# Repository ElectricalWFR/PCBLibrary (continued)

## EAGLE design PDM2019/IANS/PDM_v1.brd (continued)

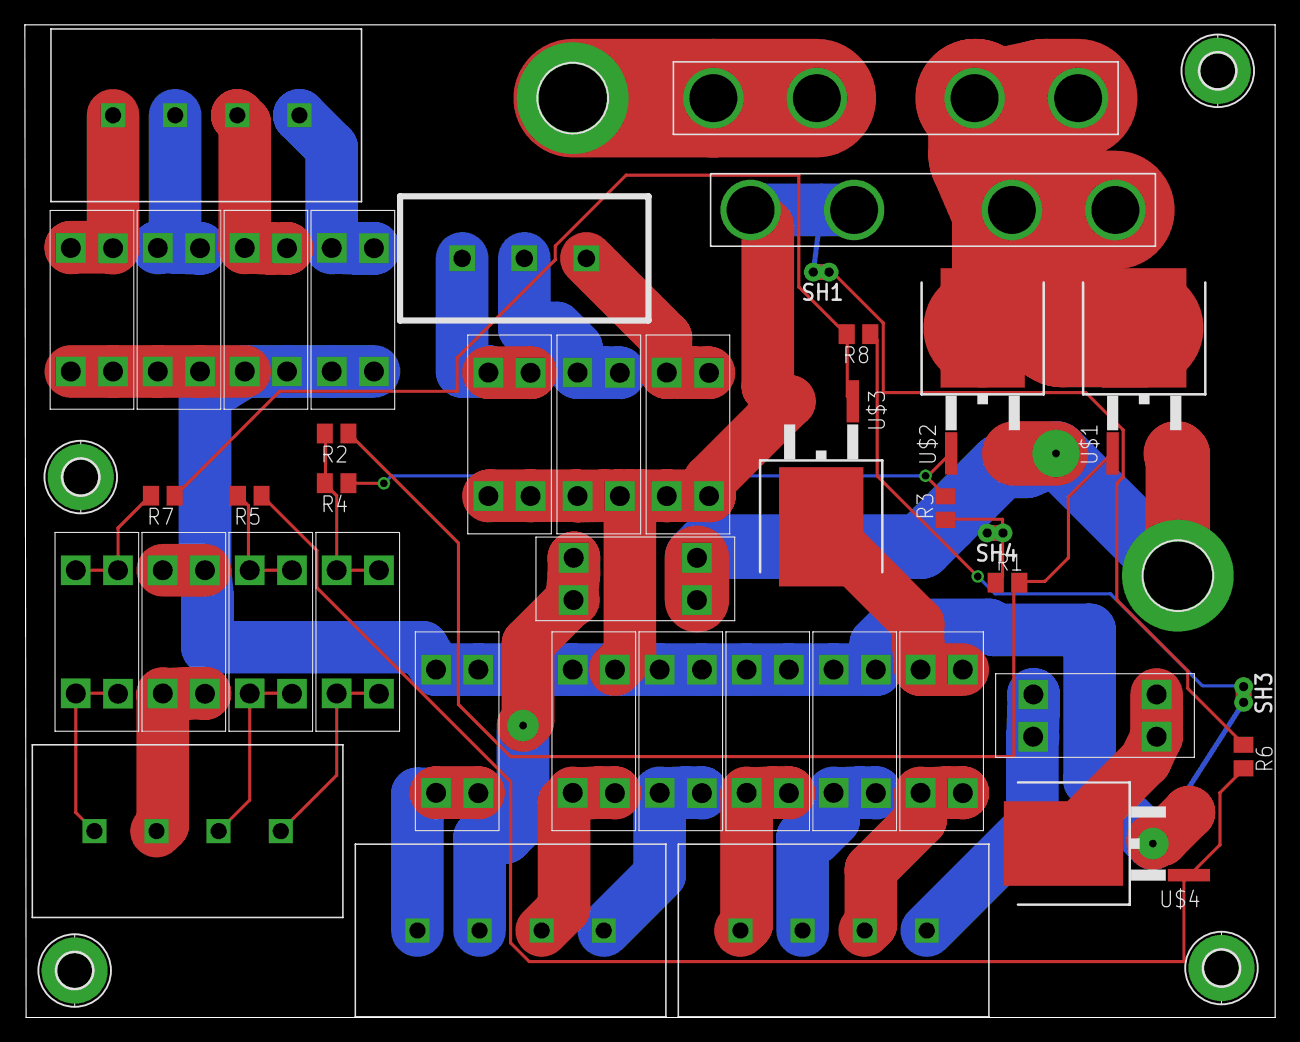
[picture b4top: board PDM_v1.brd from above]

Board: 2 copper layers, 100.6 x 79.9 mm, 47 parts (0 on the bottom side), 35 nets.

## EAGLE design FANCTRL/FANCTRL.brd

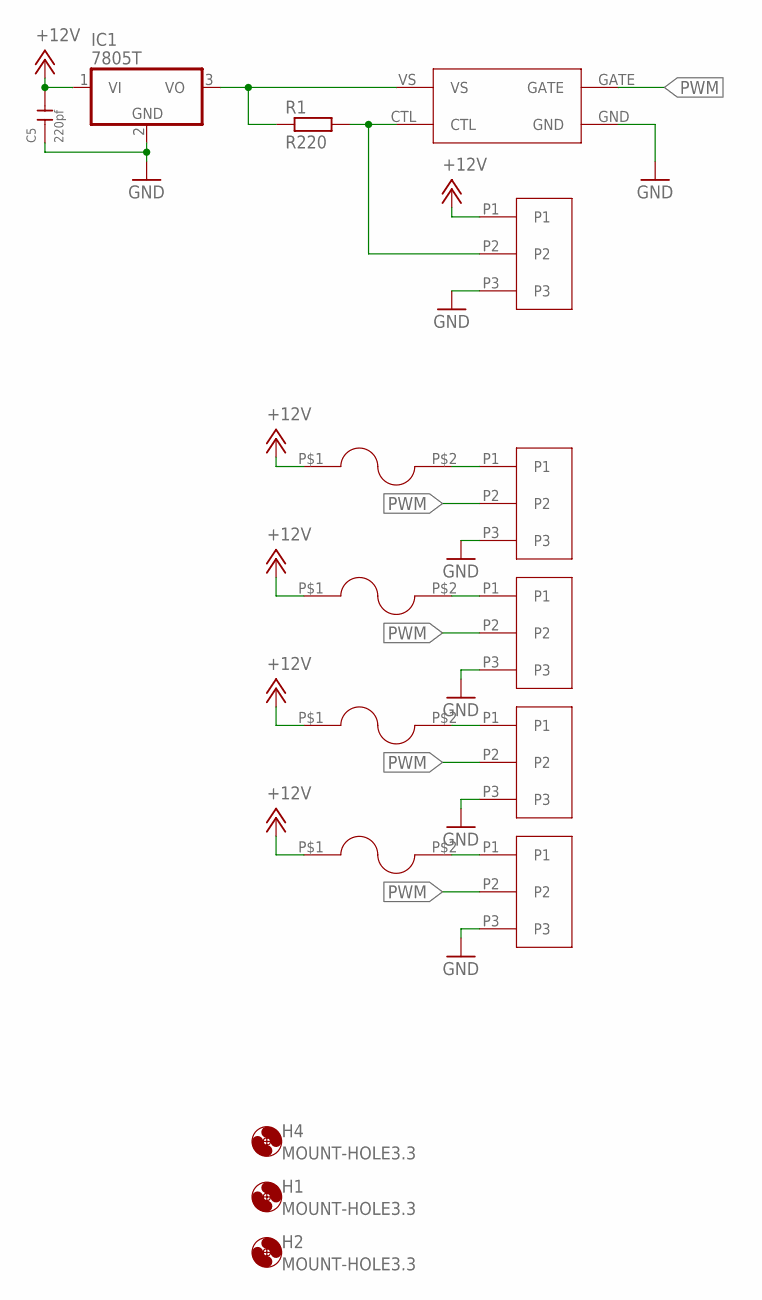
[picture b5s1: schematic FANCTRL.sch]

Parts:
C5: 220pf; C0402
H1, H2, H4: MOUNT-HOLE3.3; 3,3
IC1: 7805T; TO220H
R1: R220; R0805
U$1, U$2, U$3, U$4, U$9: 1935789
U$5, U$6, U$7, U$8: 2920L400/15MR
U$15: MIC4417; PDM_2019_REVB_MIC4416YM4-TR

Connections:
+12V: C5.2, IC1.1 (VI), U$1.P1, U$5.P$1, U$6.P$1, U$7.P$1, U$8.P$1
GND: C5.1, IC1.2 (GND), U$1.P3, U$2.P3, U$3.P3, U$4.P3, U$9.P3, U$15.GND
unnamed: U$2.P1, U$5.P$2
unnamed: U$3.P1, U$6.P$2
unnamed: U$4.P1, U$7.P$2
unnamed: U$8.P$2, U$9.P1
unnamed: IC1.3 (VO), R1.1, U$15.VS
unnamed: R1.2, U$1.P2, U$15.CTL
PWM: U$2.P2, U$3.P2, U$4.P2, U$9.P2, U$15.GATE

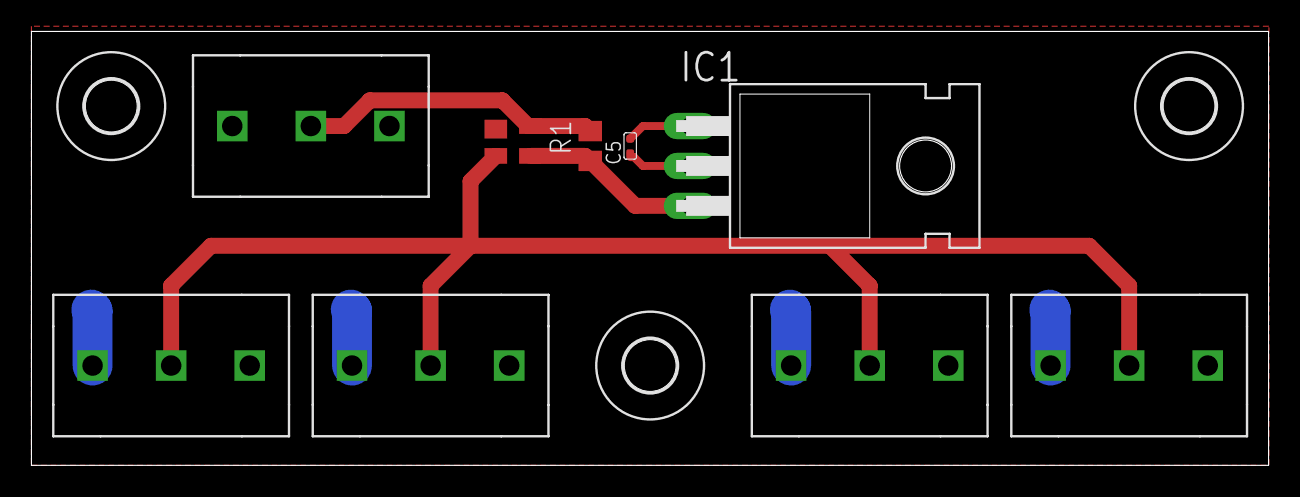
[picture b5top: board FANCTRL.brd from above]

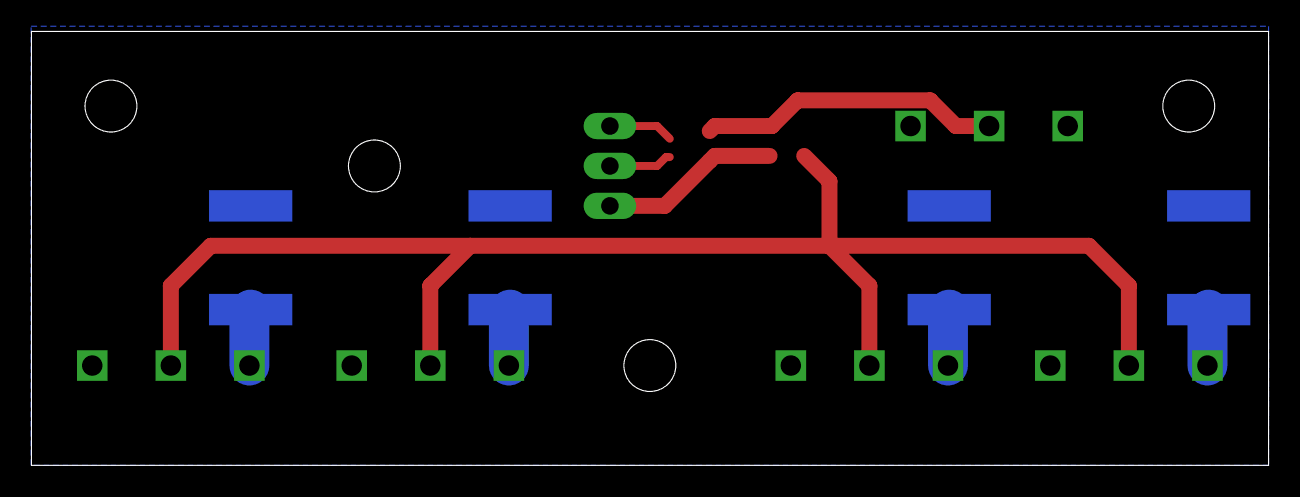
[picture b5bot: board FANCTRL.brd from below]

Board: 2 copper layers, 78.7 x 27.6 mm, 16 parts (4 on the bottom side), 9 nets.

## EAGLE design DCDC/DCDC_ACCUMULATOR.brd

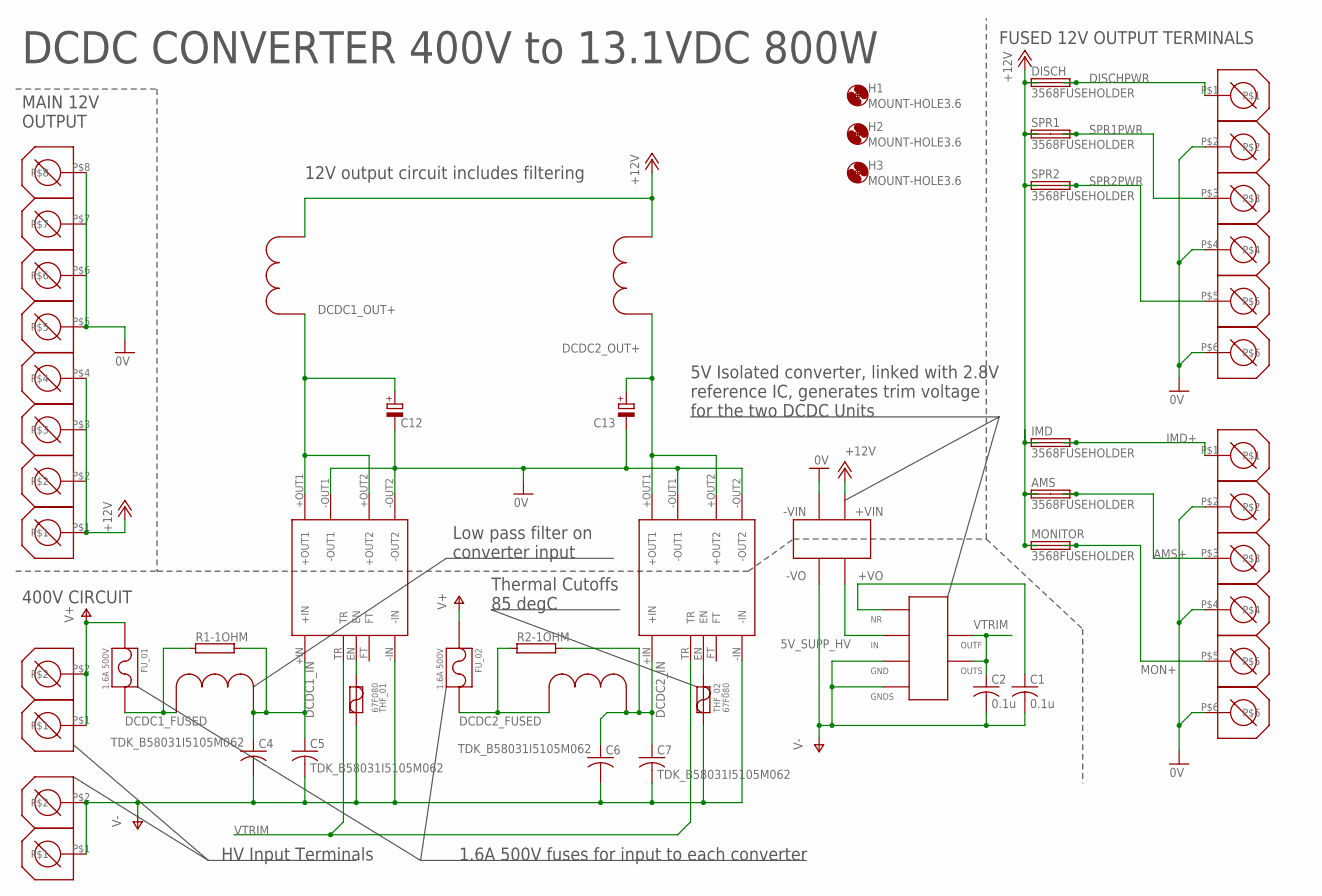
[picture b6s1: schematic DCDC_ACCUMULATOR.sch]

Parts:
AMS: 3568FUSEHOLDER; 3568
C1, C2: 0.1u; C0805
C4, C5, C6, C7: TDK_B58031I5105M062; TDK_CERALINK_USTYLE
C12, C13: CPOL-EUE7.5-16; E7,5-16
DISCH: 3568FUSEHOLDER; 3568
FU_01, FU_02: 1.6A 500V; LF_885
H1, H2, H3: MOUNT-HOLE3.6; 3,6
IMD: 3568FUSEHOLDER; 3568
MONITOR: 3568FUSEHOLDER; 3568
R1-1OHM, R2-1OHM: RMG100-V; TO-247-2V
SPR1, SPR2: 3568FUSEHOLDER; 3568
THF_01, THF_02: 67F080; TO220ACS
U$1, U$4: DCM4623TD2J13D0T00; VICOR_DCM4623TD2J13D0T00
U$2, U$5: P1330-102H; P1330
U$3, U$6: MPC1250LR36C; MPC1250LR
U$9: MURATA_MEV1S1205SC; MEV_7_PIN_SIP
U$10: MAXIM_MAX6126A28; UMAX
U$13: 1777600_PHOENIX; 1777600_FOOT
U$14, U$15: 1935200_PHOENIX; 1777587_FOOT
U$16, U$17: 282838-2_TE; 282838-2_FOOT

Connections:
0V: C12.-, C13.-, U$1.-OUT1, U$1.-OUT2, U$4.-OUT1, U$4.-OUT2, U$9.-VIN, U$13.P$5, U$13.P$6, U$13.P$7, U$13.P$8, U$14.P$2, U$14.P$4, U$14.P$6, U$15.P$2, U$15.P$4, U$15.P$6
5V_SUPP_HV: U$9.+VOUT (+VO), U$10.2 (IN)
+12V: AMS.L1 (1A), AMS.L2 (1B), DISCH.L1 (1A), DISCH.L2 (1B), IMD.L1 (1A), IMD.L2 (1B), MONITOR.L1 (1A), MONITOR.L2 (1B), SPR1.L1 (1A), SPR1.L2 (1B), SPR2.L1 (1A), SPR2.L2 (1B), U$3.P$2, U$6.P$2, U$9.+VIN, U$13.P$1, U$13.P$2, U$13.P$3, U$13.P$4
AMS+: AMS.R1 (2A), AMS.R2 (2B), U$15.P$3
DCDC1_FUSED: FU_01.P$2, R1-1OHM.1, U$2.P$1
DCDC1_IN: C4.P$1 (1), C5.P$1 (1), R1-1OHM.2, U$1.+IN, U$2.P$2
DCDC1_OUT+: C12.+, U$1.+OUT1, U$1.+OUT2, U$3.P$1
DCDC1_TEMP_DISABLE: THF_01.C, U$1.EN
DCDC2_FUSED: FU_02.P$2, R2-1OHM.1, U$5.P$1
DCDC2_IN: C6.P$1 (1), C7.P$1 (1), R2-1OHM.2, U$4.+IN, U$5.P$2
DCDC2_OUT+: C13.+, U$4.+OUT1, U$4.+OUT2, U$6.P$1
DCDC2_TEMP_DISABLE: THF_02.C, U$4.EN
DISCHPWR: DISCH.R1 (2A), DISCH.R2 (2B), U$14.P$1
IMD+: IMD.R1 (2A), IMD.R2 (2B), U$15.P$1
MON+: MONITOR.R1 (2A), MONITOR.R2 (2B), U$15.P$5
SPR1PWR: SPR1.R1 (2A), SPR1.R2 (2B), U$14.P$3
SPR2PWR: SPR2.R1 (2A), SPR2.R2 (2B), U$14.P$5
V+: FU_01.P$1, FU_02.P$1, U$16.P$1, U$16.P$2
V-: C1.2, C2.2, C4.P$2 (2), C5.P$2 (2), C6.P$2 (2), C7.P$2 (2), THF_01.A, THF_02.A, U$1.-IN, U$4.-IN, U$9.-VOUT (-VO), U$10.3 (GND), U$10.4 (GNDS), U$17.P$1, U$17.P$2
VREF_NR: C1.1, U$10.1 (NR)
VTRIM: C2.1, U$1.TR, U$4.TR, U$10.6 (OUTS), U$10.7 (OUTF)

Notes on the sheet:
DCDC CONVERTER 400V to 13.1VDC 800W
FUSED 12V OUTPUT TERMINALS
MAIN 12V OUTPUT
400V CIRCUIT
12V output circuit includes filtering
5V Isolated converter, linked with 2.8V reference IC, generates trim voltage for the two DCDC Units
HV Input Terminals
1.6A 500V fuses for input to each converter
Thermal Cutoffs 85 degC
Low pass filter on converter input

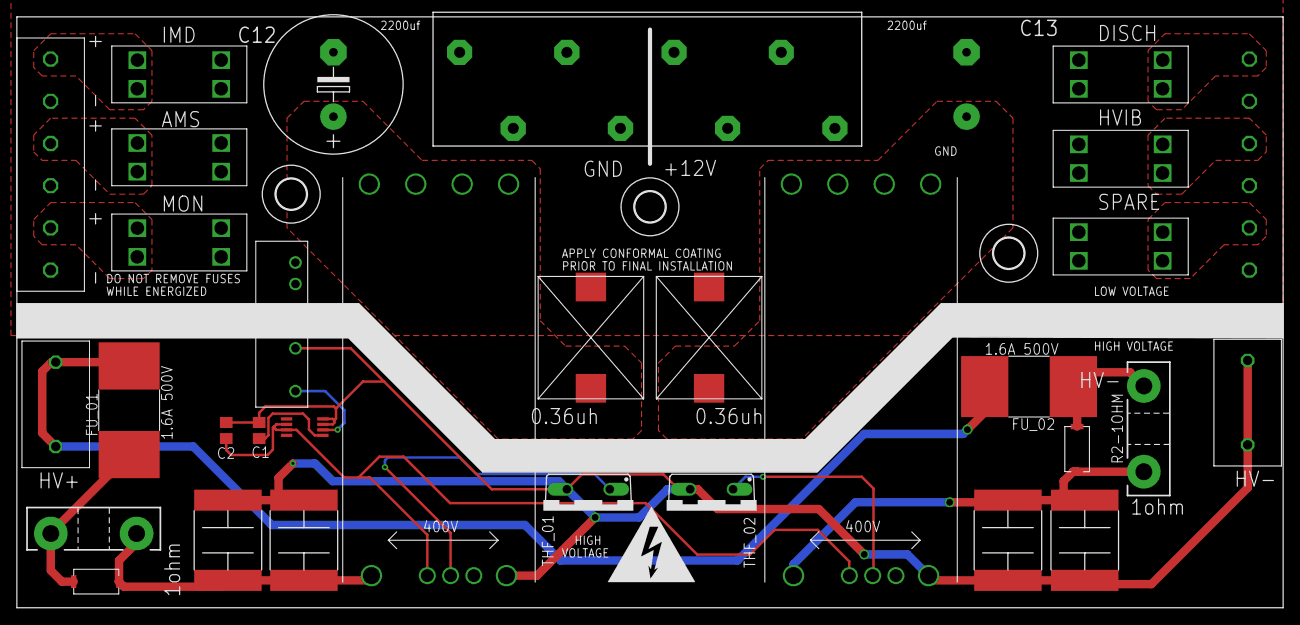
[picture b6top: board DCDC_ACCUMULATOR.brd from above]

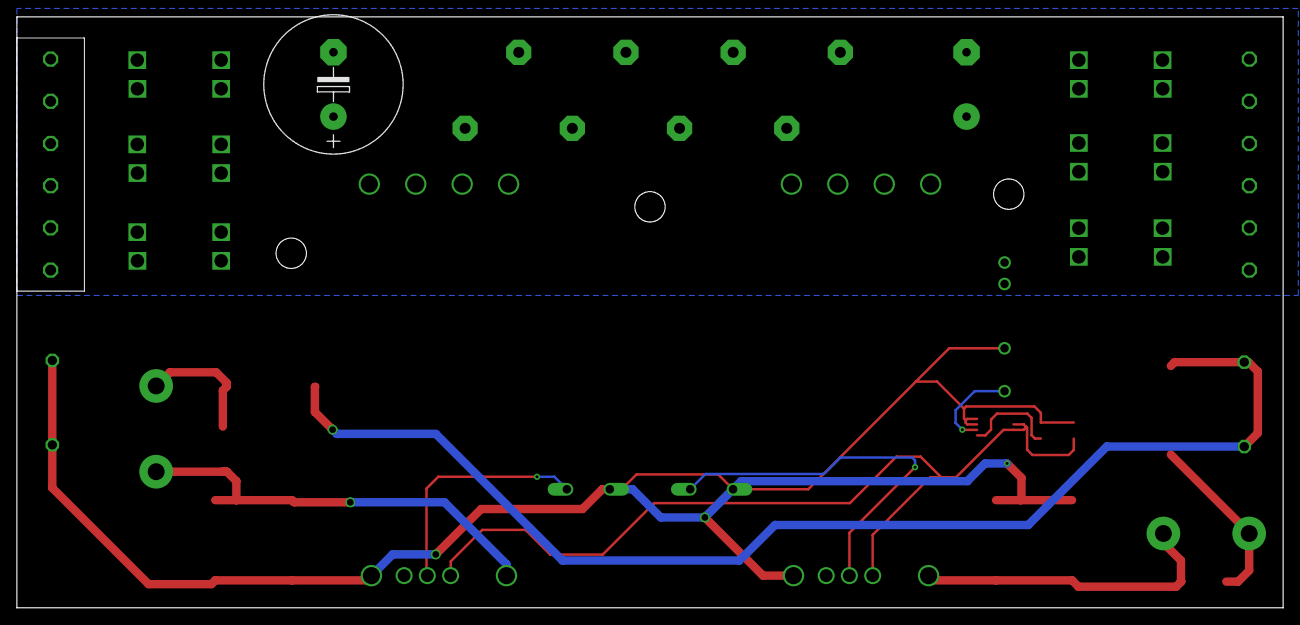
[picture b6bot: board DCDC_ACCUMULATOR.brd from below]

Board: 2 copper layers, 150.0 x 70.0 mm, 36 parts (2 on the bottom side), 21 nets.

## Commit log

2019-03-15 Added boards
2019-03-15 Removed Backups
